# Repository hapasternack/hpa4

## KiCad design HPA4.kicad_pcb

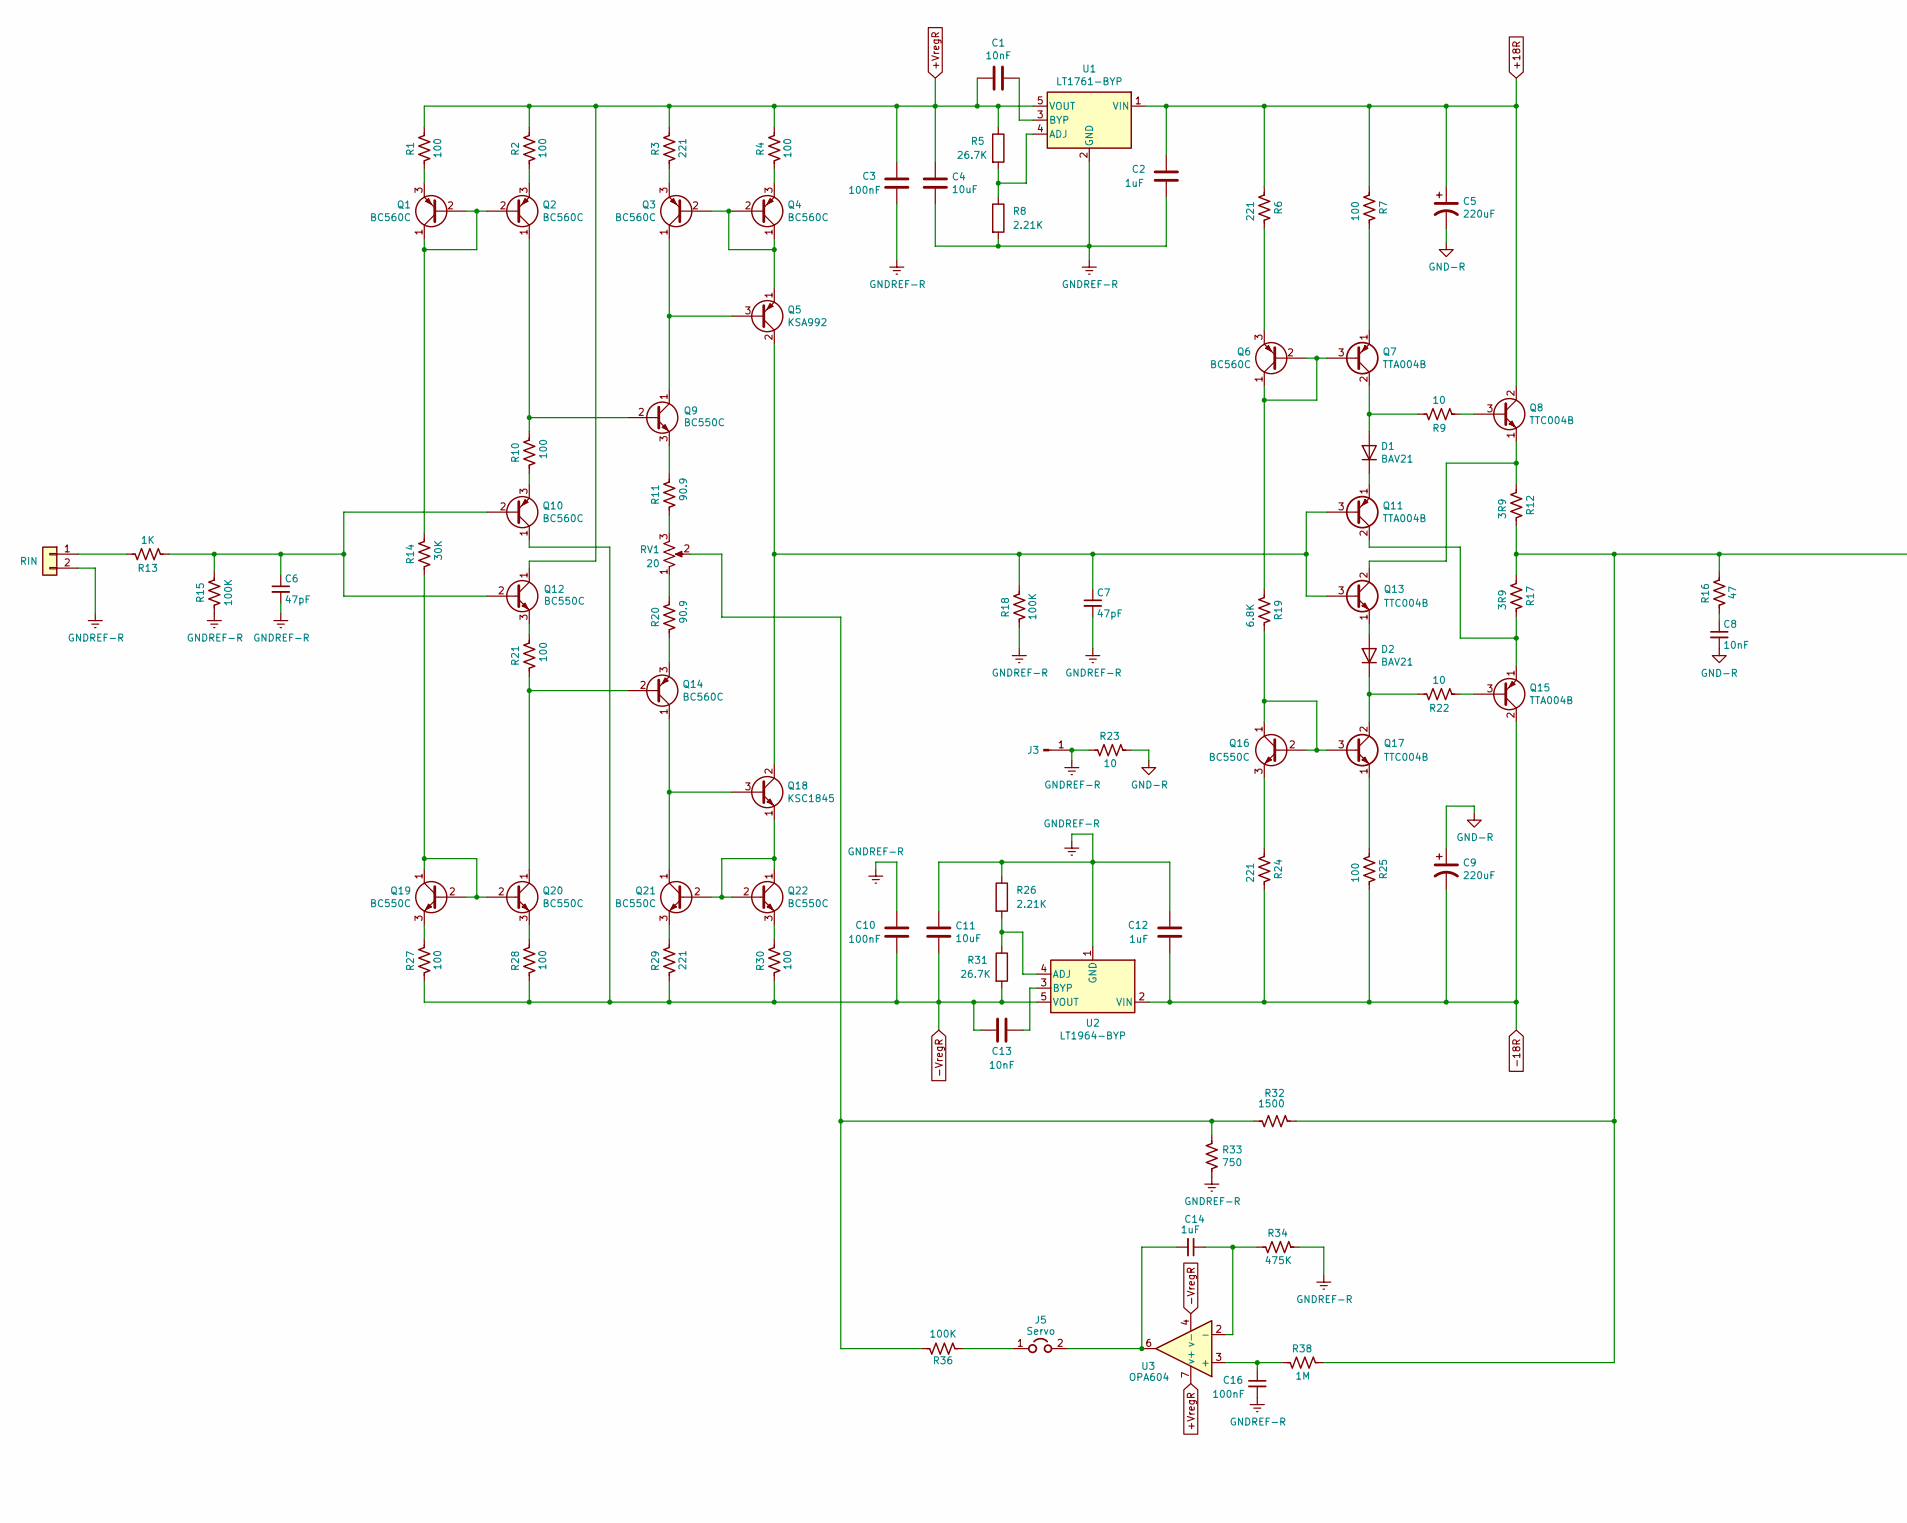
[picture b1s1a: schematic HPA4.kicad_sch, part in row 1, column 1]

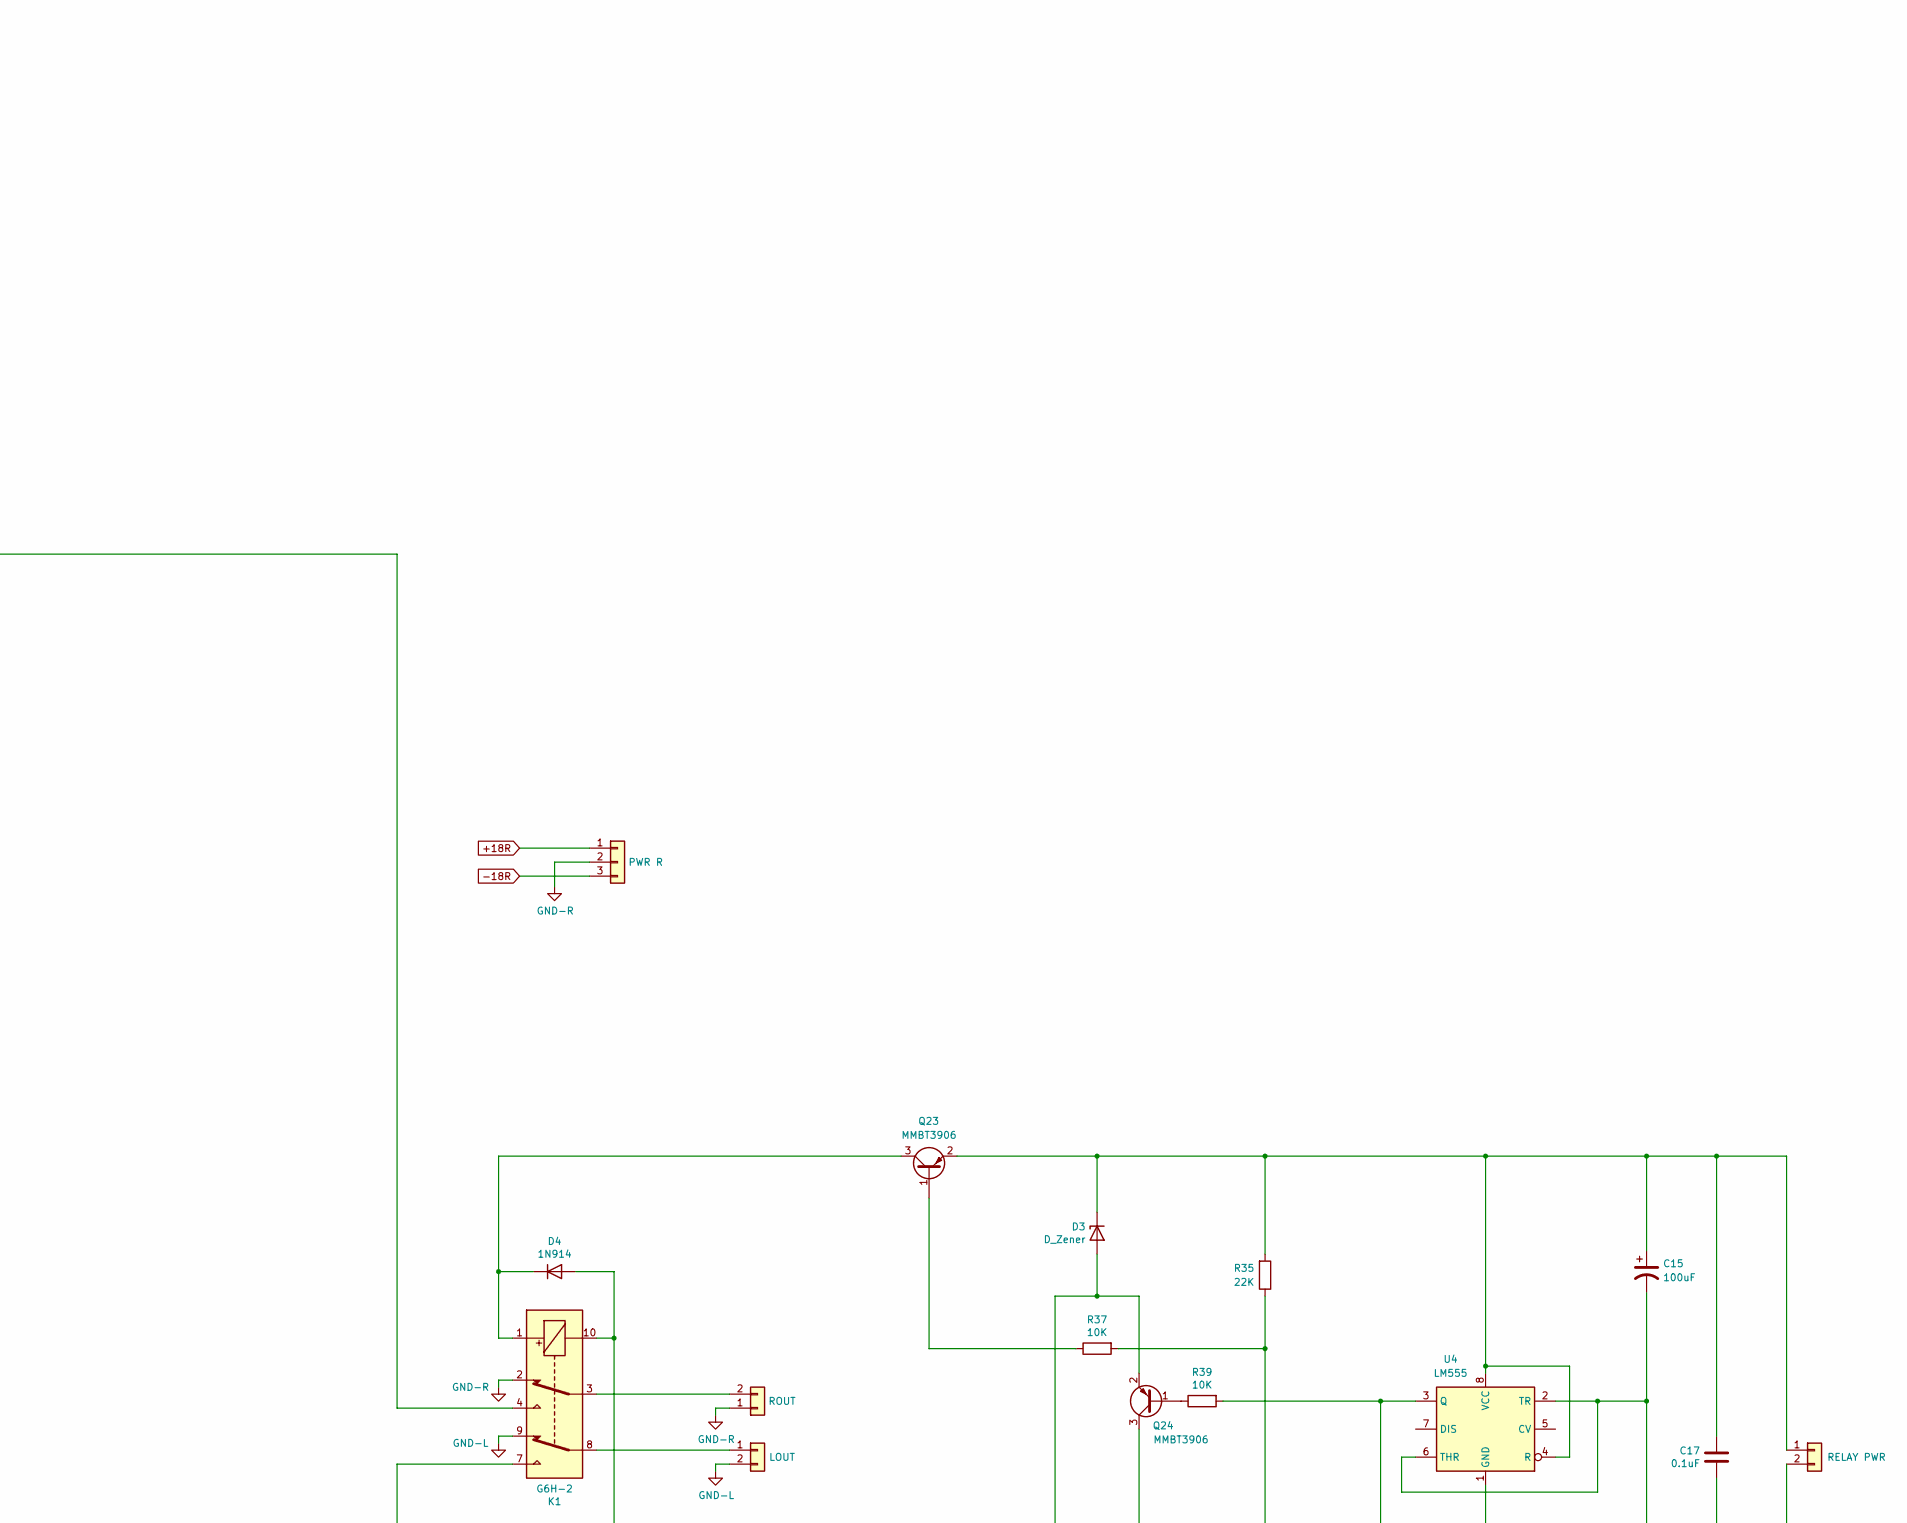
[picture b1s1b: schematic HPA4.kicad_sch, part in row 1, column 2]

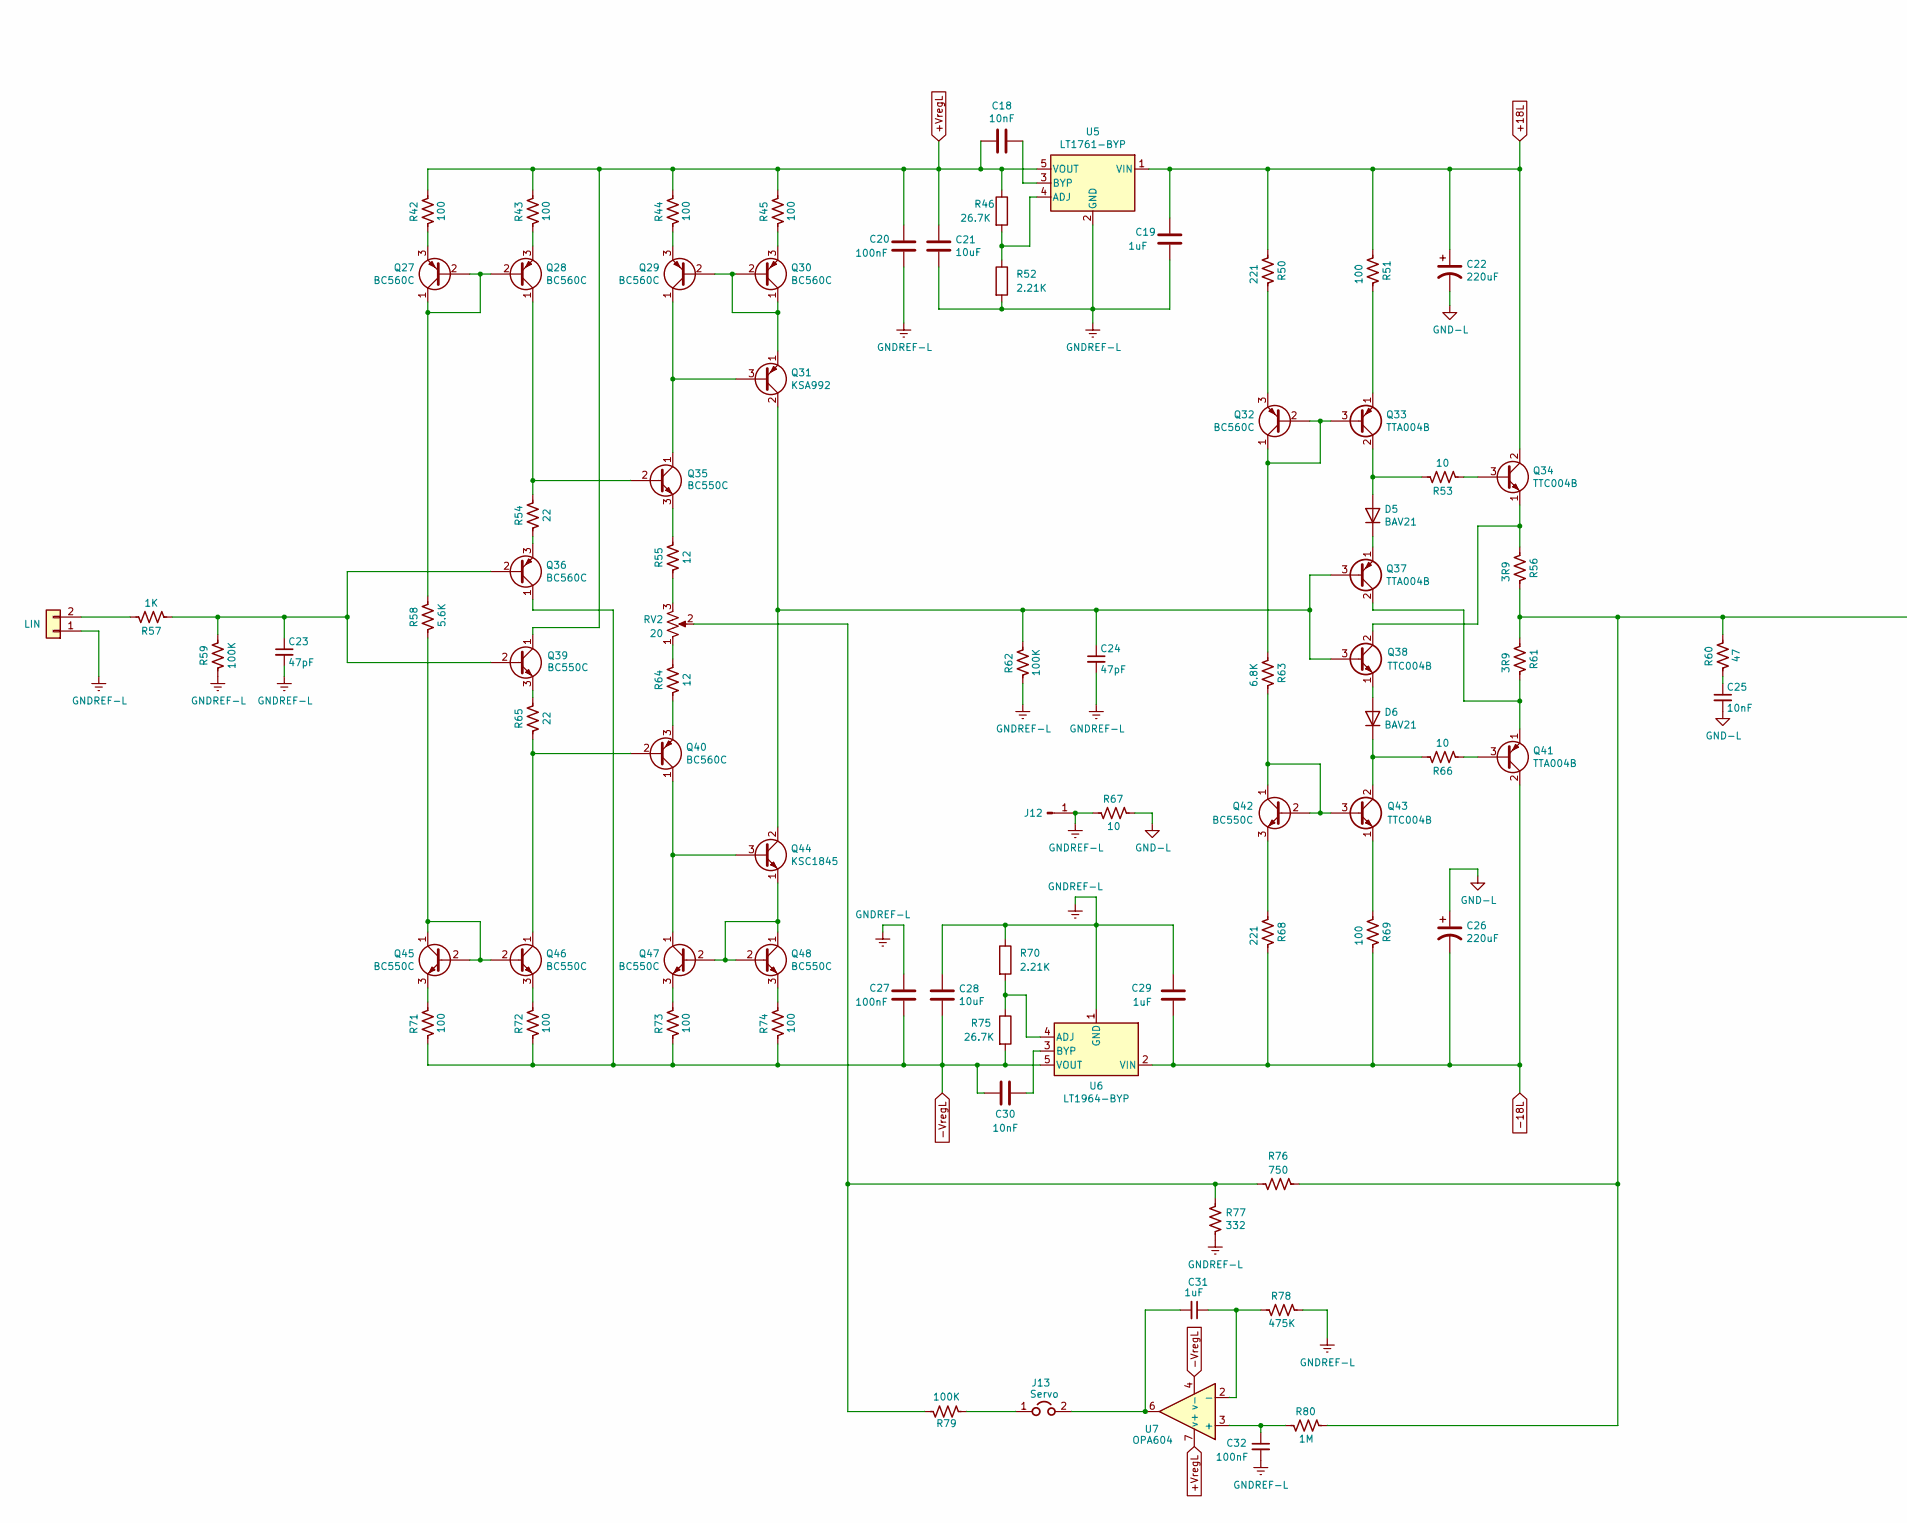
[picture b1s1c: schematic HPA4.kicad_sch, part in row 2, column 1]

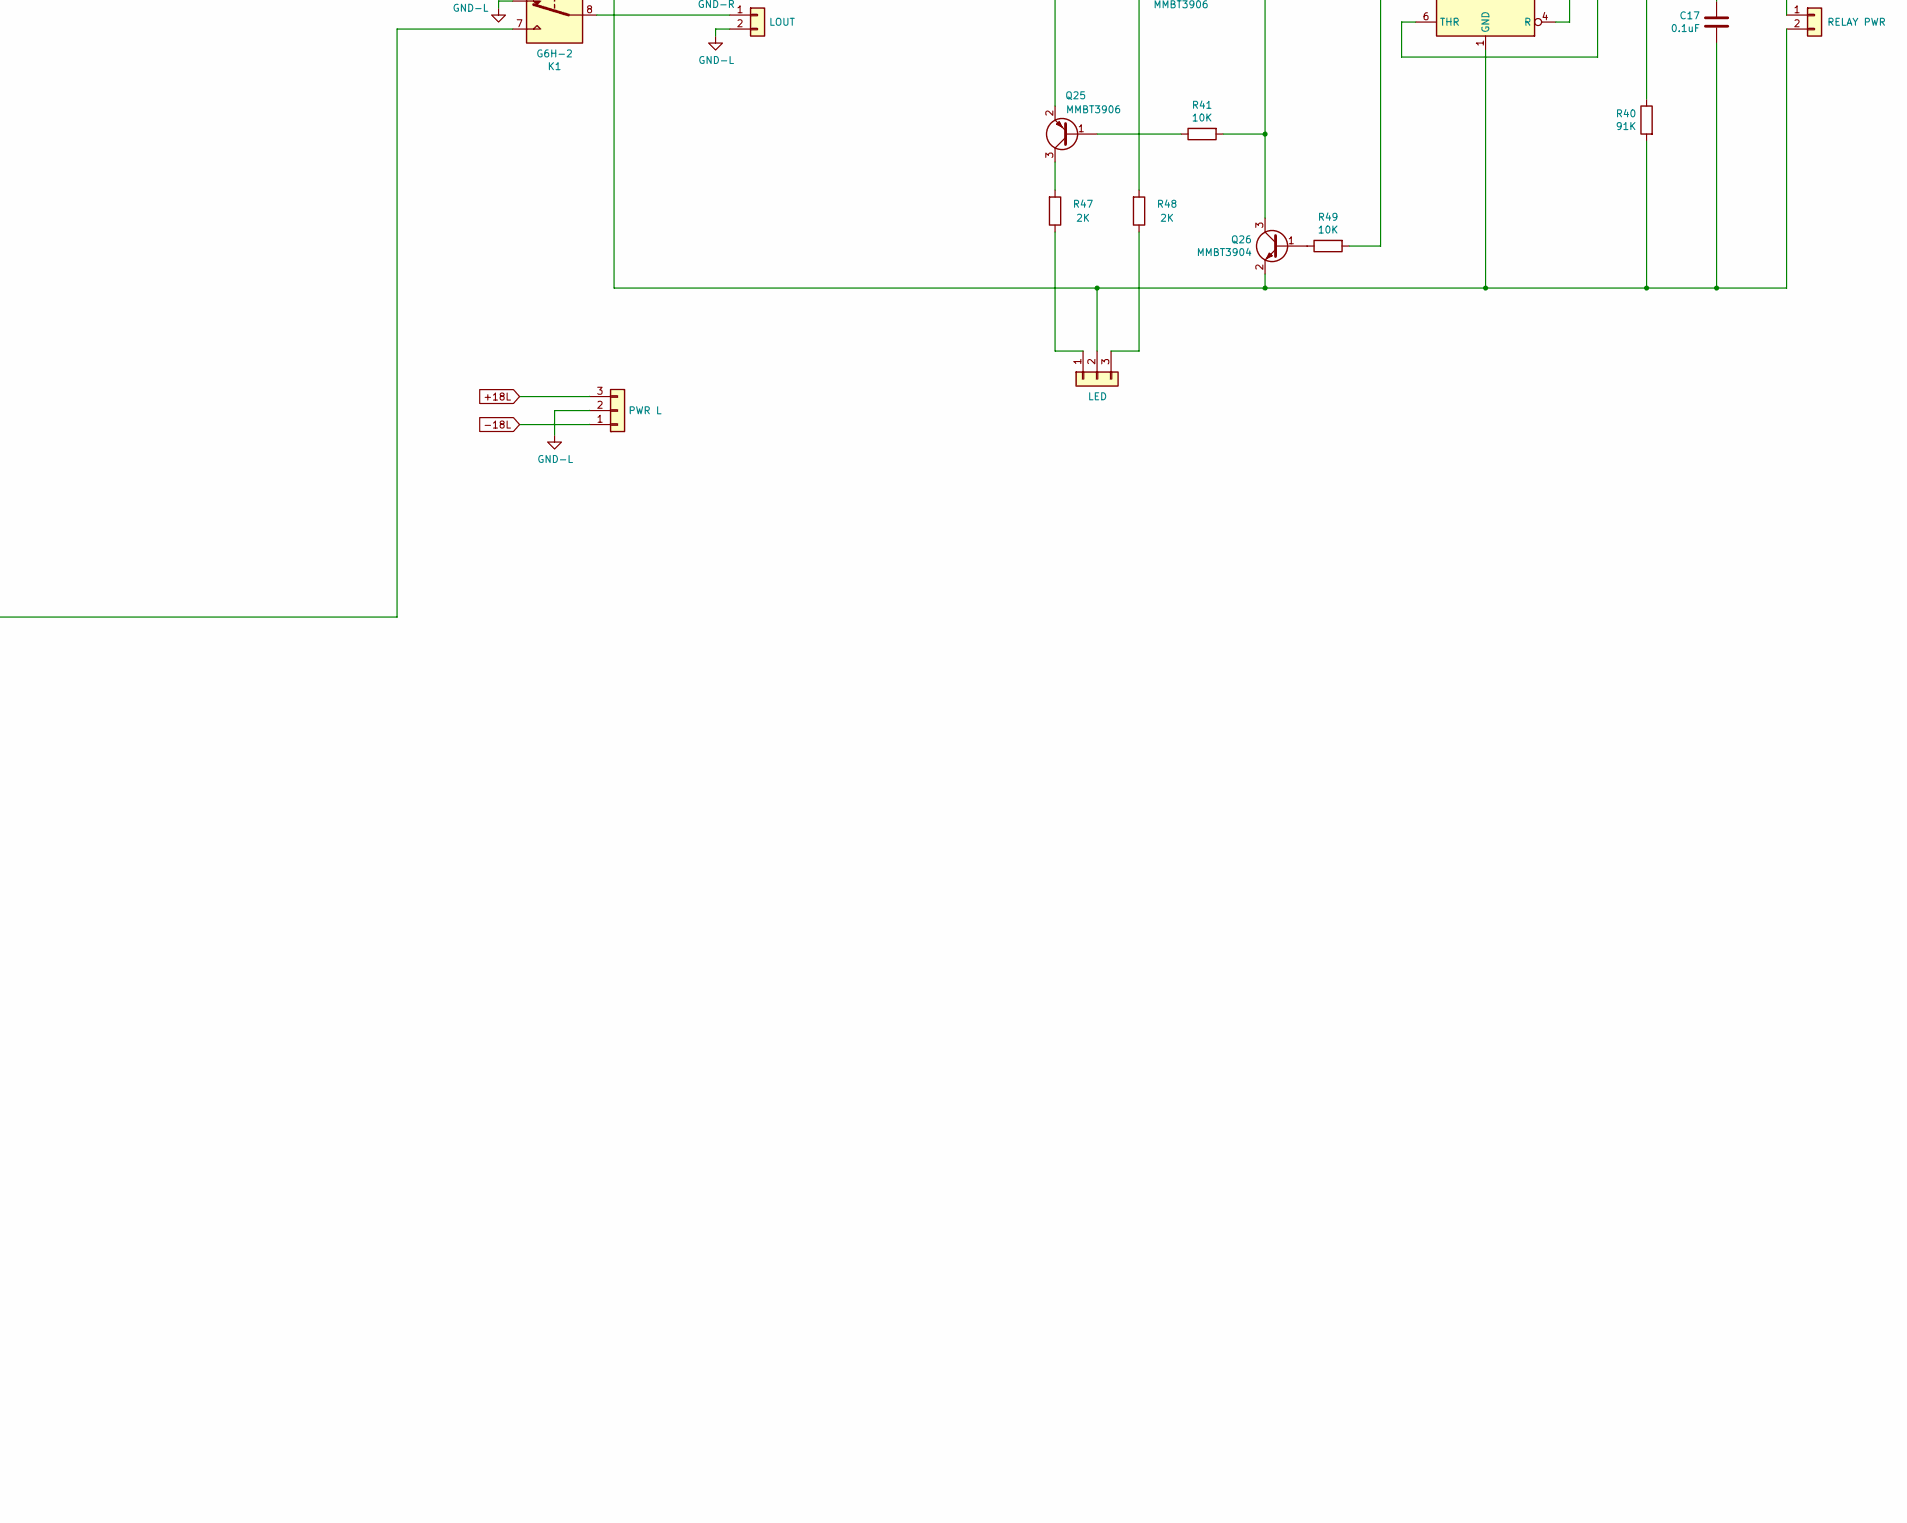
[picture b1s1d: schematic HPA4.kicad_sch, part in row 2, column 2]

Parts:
C1, C13, C18, C30: 10nF; C_0805_2012Metric
C2, C12, C19, C29: 1uF; C_0805_2012Metric
C3, C10, C16, C20, C27, C32: 100nF; C_Rect_L7.2mm_W2.5mm_P5.00mm_FKS2_FKP2_MKS2_MKP2
C4, C11, C21, C28: 10uF; C_0805_2012Metric
C5, C9, C22, C26: 220uF; CP_Radial_D10.0mm_P5.00mm
C6, C7, C23, C24: 47pF; C_Rect_L7.2mm_W4.5mm_P5.00mm_FKS2_FKP2_MKS2_MKP2
C8, C25: 10nF; C_Rect_L7.2mm_W2.5mm_P5.00mm_FKS2_FKP2_MKS2_MKP2
C14, C31: 1uF; C_Rect_L7.2mm_W5.5mm_P5.00mm_FKS2_FKP2_MKS2_MKP2
C15: 100uF; CP_Elec_5x5.9
C17: 0.1uF; C_1206_3216Metric_Pad1.33x1.80mm_HandSolder
D1, D2, D5, D6: BAV21; D_DO-35_SOD27_P7.62mm_Horizontal
D3: D_Zener; D_1206_3216Metric_Pad1.42x1.75mm_HandSolder
D4: 1N914; D_DO-35_SOD27_P7.62mm_Horizontal
J2: RIN; Molex-22-11-2022-2-Pin-Header
J3, J12: Conn_01x01_Male; 1-pad-wire-connector-22-ga
J4: PWR R; Molex-41791-0850-3-Pin-Header
J5, J13: Servo; PinHeader_1x02_P2.54mm_Vertical
J6: ROUT; Molex-41791-0849-2-Pin-Header
J7: LOUT; Molex-41791-0849-2-Pin-Header
J8: RELAY PWR; Molex-22-11-2022-2-Pin-Header
J9: LED; Molex-22-11-2032-3-Pin-Header
J10: PWR L; Molex-41791-0850-3-Pin-Header
J11: LIN; Molex-22-11-2022-2-Pin-Header
K1: G6H-2; Relay_DPDT_Omron_G6H-2
Q1, Q2, Q3, Q4, Q6, Q10, Q14, Q27, Q28, Q29, Q30, Q32, Q36, Q40: BC560C; TO-92
Q5, Q31: KSA992; TO-92
Q7, Q11, Q15, Q33, Q37, Q41: TTA004B; TO-126-3_Vertical
Q8, Q13, Q17, Q34, Q38, Q43: TTC004B; TO-126-3_Vertical
Q9, Q12, Q16, Q19, Q20, Q21, Q22, Q35, Q39, Q42, Q45, Q46, Q47, Q48: BC550C; TO-92
Q18, Q44: KSC1845; TO-92
Q23, Q24, Q25: MMBT3906; SOT-23
Q26: MMBT3904; SOT-23
R1, R2, R4, R7, R10, R21, R25, R27, R28, R30, R42, R43, R44, R45, R51, R69, R71, R72, R73, R74: 100; R_Axial_DIN0207_L6.3mm_D2.5mm_P10.16mm_Horizontal
R3, R6, R24, R29, R50, R68: 221; R_Axial_DIN0207_L6.3mm_D2.5mm_P10.16mm_Horizontal
R5, R31, R46, R75: 26.7K; R_0805_2012Metric
R8, R26, R52, R70: 2.21K; R_0805_2012Metric
R9, R22, R23, R53, R66, R67: 10; R_Axial_DIN0207_L6.3mm_D2.5mm_P10.16mm_Horizontal
R11, R20: 90.9; R_Axial_DIN0207_L6.3mm_D2.5mm_P10.16mm_Horizontal
R12, R17, R56, R61: 3R9; R_Axial_DIN0411_L9.9mm_D3.6mm_P12.70mm_Horizontal
R13, R57: 1K; R_Axial_DIN0207_L6.3mm_D2.5mm_P10.16mm_Horizontal
R14: 30K; R_Axial_DIN0207_L6.3mm_D2.5mm_P10.16mm_Horizontal
R15, R18, R36, R59, R62, R79: 100K; R_Axial_DIN0207_L6.3mm_D2.5mm_P10.16mm_Horizontal
R16, R60: 47; R_Axial_DIN0207_L6.3mm_D2.5mm_P10.16mm_Horizontal
R19, R63: 6.8K; R_Axial_DIN0207_L6.3mm_D2.5mm_P10.16mm_Horizontal
R32: 1500; R_Axial_DIN0207_L6.3mm_D2.5mm_P10.16mm_Horizontal
R33, R76: 750; R_Axial_DIN0207_L6.3mm_D2.5mm_P10.16mm_Horizontal
R34, R78: 475K; R_0805_2012Metric
R35: 22K; R_1206_3216Metric
R37, R39, R41, R49: 10K; R_1206_3216Metric
R38, R80: 1M; R_0805_2012Metric
R40: 91K; R_1206_3216Metric
R47, R48: 2K; R_1206_3216Metric
R54, R65: 22; R_Axial_DIN0207_L6.3mm_D2.5mm_P10.16mm_Horizontal
R55, R64: 12; R_Axial_DIN0207_L6.3mm_D2.5mm_P10.16mm_Horizontal
R58: 5.6K; R_Axial_DIN0207_L6.3mm_D2.5mm_P10.16mm_Horizontal
R77: 332; R_Axial_DIN0207_L6.3mm_D2.5mm_P10.16mm_Horizontal
RV1, RV2: 20; Potentiometer_Bourns_3296Y_Vertical
U1, U5: LT1761-BYP; TSOT-23-5
U2, U6: LT1964-BYP; TSOT-23-5
U3, U7: OPA604; SOIC-8_3.9x4.9mm_P1.27mm
U4: LM555; SOIC-8_3.9x4.9mm_P1.27mm

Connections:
+18L: C19.1, C22.1, J10.3, Q34.2 (C), R50.2, R51.2, U5.1 (VIN)
+18R: C2.1, C5.1, J4.1, Q8.2 (C), R6.2, R7.2, U1.1 (VIN)
+VregL: C18.2, C20.1, C21.1, Q39.1 (C), R42.1, R43.1, R44.1, R45.1, R46.1, U5.5 (VOUT), U7.7 (v+)
+VregR: C1.2, C3.1, C4.1, Q12.1 (C), R1.1, R2.1, R3.1, R4.1, R5.1, U1.5 (VOUT), U3.7 (v+)
-18L: C26.2, C29.1, J10.1, Q41.2 (C), R68.1, R69.1, U6.2 (VIN)
-18R: C9.2, C12.1, J4.3, Q15.2 (C), R24.1, R25.1, U2.2 (VIN)
-VregL: C27.2, C28.2, C30.2, Q36.1 (C), R71.2, R72.2, R73.2, R74.2, R75.2, U6.5 (VOUT), U7.4 (v-)
-VregR: C10.2, C11.2, C13.2, Q10.1 (C), R27.2, R28.2, R29.2, R30.2, R31.2, U2.5 (VOUT), U3.4 (v-)
GND-L: C22.2, C25.2, C26.1, J7.2, J10.2, K1.9, R67.1
GND-R: C5.2, C8.2, C9.1, J4.2, J6.1, K1.2, R23.1
GNDREF-L: C19.2, C20.2, C21.2, C23.2, C24.2, C27.1, C28.1, C29.2, C32.2, J11.1, J12.1, R52.2, R59.2, R62.2, R67.2, R70.1, R77.2, R78.1, U5.2 (GND), U6.1 (GND)
GNDREF-R: C2.2, C3.2, C4.2, C6.2, C7.2, C10.1, C11.1, C12.2, C16.2, J2.2, J3.1, R8.2, R15.2, R18.2, R23.2, R26.1, R33.2, R34.1, U1.2 (GND), U2.1 (GND)
unnamed: C1.1, U1.3 (BYP)
unnamed: C6.1, Q10.2 (B), Q12.2 (B), R13.2, R15.1
unnamed: C7.1, Q5.2 (C), Q11.3 (B), Q13.3 (B), Q18.2 (C), R18.1
unnamed: C8.1, R16.2
unnamed: C13.1, U2.3 (BYP)
unnamed: C14.1, R34.2, U3.2 (-)
unnamed: C14.2, J5.2, U3.6
unnamed: C15.1, C17.1, D3.1 (K), J8.1, Q23.2 (E), R35.2, U4.4 (R), U4.8 (VCC)
unnamed: C15.2, R40.1, U4.2 (TR), U4.6 (THR)
unnamed: C16.1, R38.2, U3.3 (+)
unnamed: C17.2, D4.2 (A), J8.2, J9.2, K1.10, Q26.2 (E), R40.2, U4.1 (GND)
unnamed: C18.1, U5.3 (BYP)
unnamed: C23.1, Q36.2 (B), Q39.2 (B), R57.2, R59.1
unnamed: C24.1, Q31.2 (C), Q37.3 (B), Q38.3 (B), Q44.2 (C), R62.1
unnamed: C25.1, R60.2
unnamed: C30.1, U6.3 (BYP)
unnamed: C31.1, R78.2, U7.2 (-)
unnamed: C31.2, J13.2, U7.6
unnamed: C32.1, R80.2, U7.3 (+)
unnamed: D1.1 (K), Q11.1 (E)
unnamed: D1.2 (A), Q7.2 (C), R9.1
unnamed: D2.1 (K), Q17.2 (C), R22.1
unnamed: D2.2 (A), Q13.1 (E)
unnamed: D3.2 (A), Q24.2 (E), Q25.2 (E)
unnamed: D4.1 (K), K1.1, Q23.3 (C)
unnamed: D5.1 (K), Q37.1 (E)
unnamed: D5.2 (A), Q33.2 (C), R53.1
unnamed: D6.1 (K), Q43.2 (C), R66.1
unnamed: D6.2 (A), Q38.1 (E)
unnamed: J2.1, R13.1
unnamed: J5.1, R36.1
unnamed: J6.2, K1.3
unnamed: J7.1, K1.8
unnamed: J9.1, R47.1
unnamed: J9.3, R48.1
unnamed: J11.2, R57.1
unnamed: J13.1, R79.1
unnamed: K1.4, R12.1, R16.1, R17.2, R32.2, R38.1
unnamed: K1.7, R56.1, R60.1, R61.2, R76.2, R80.1
unnamed: Q1.1 (C), Q1.2 (B), Q2.2 (B), R14.1
unnamed: Q1.3 (E), R1.2
unnamed: Q2.1 (C), Q9.2 (B), R10.1
unnamed: Q2.3 (E), R2.2
unnamed: Q3.1 (C), Q5.3 (B), Q9.1 (C)
unnamed: Q3.2 (B), Q4.1 (C), Q4.2 (B), Q5.1 (E)
unnamed: Q3.3 (E), R3.2
unnamed: Q4.3 (E), R4.2
unnamed: Q6.1 (C), Q6.2 (B), Q7.3 (B), R19.2
unnamed: Q6.3 (E), R6.1
unnamed: Q7.1 (E), R7.1
unnamed: Q8.3 (B), R9.2
unnamed: Q9.3 (E), R11.1
unnamed: Q10.3 (E), R10.2
unnamed: Q11.2 (C), Q15.1 (E), R17.1
unnamed: Q12.3 (E), R21.1
unnamed: Q8.1 (E), Q13.2 (C), R12.2
unnamed: Q14.1 (C), Q18.3 (B), Q21.1 (C)
unnamed: Q14.2 (B), Q20.1 (C), R21.2
unnamed: Q14.3 (E), R20.2
unnamed: Q15.3 (B), R22.2
unnamed: Q16.1 (C), Q16.2 (B), Q17.3 (B), R19.1
unnamed: Q16.3 (E), R24.2
unnamed: Q17.1 (E), R25.2
unnamed: Q18.1 (E), Q21.2 (B), Q22.1 (C), Q22.2 (B)
unnamed: Q19.1 (C), Q19.2 (B), Q20.2 (B), R14.2
unnamed: Q19.3 (E), R27.1
unnamed: Q20.3 (E), R28.1
unnamed: Q21.3 (E), R29.1
unnamed: Q22.3 (E), R30.1
unnamed: Q23.1 (B), R37.1
unnamed: Q24.1 (B), R39.1
unnamed: Q24.3 (C), R48.2
unnamed: Q25.1 (B), R41.1
unnamed: Q25.3 (C), R47.2
unnamed: Q26.1 (B), R49.1
unnamed: Q26.3 (C), R35.1, R37.2, R41.2
unnamed: Q27.1 (C), Q27.2 (B), Q28.2 (B), R58.1
unnamed: Q27.3 (E), R42.2
unnamed: Q28.1 (C), Q35.2 (B), R54.1
unnamed: Q28.3 (E), R43.2
unnamed: Q29.1 (C), Q31.3 (B), Q35.1 (C)
unnamed: Q29.2 (B), Q30.1 (C), Q30.2 (B), Q31.1 (E)
unnamed: Q29.3 (E), R44.2
unnamed: Q30.3 (E), R45.2
unnamed: Q32.1 (C), Q32.2 (B), Q33.3 (B), R63.2
unnamed: Q32.3 (E), R50.1
unnamed: Q33.1 (E), R51.1
unnamed: Q34.1 (E), Q38.2 (C), R56.2
unnamed: Q34.3 (B), R53.2
unnamed: Q35.3 (E), R55.1
unnamed: Q36.3 (E), R54.2
unnamed: Q37.2 (C), Q41.1 (E), R61.1
unnamed: Q39.3 (E), R65.1
unnamed: Q40.1 (C), Q44.3 (B), Q47.1 (C)
unnamed: Q40.2 (B), Q46.1 (C), R65.2
unnamed: Q40.3 (E), R64.2
unnamed: Q41.3 (B), R66.2
unnamed: Q42.1 (C), Q42.2 (B), Q43.3 (B), R63.1
unnamed: Q42.3 (E), R68.2
unnamed: Q43.1 (E), R69.2
unnamed: Q44.1 (E), Q47.2 (B), Q48.1 (C), Q48.2 (B)
unnamed: Q45.1 (C), Q45.2 (B), Q46.2 (B), R58.2
unnamed: Q45.3 (E), R71.1
unnamed: Q46.3 (E), R72.1
unnamed: Q47.3 (E), R73.1
unnamed: Q48.3 (E), R74.1
unnamed: R5.2, R8.1, U1.4 (ADJ)
unnamed: R11.2, RV1.3
unnamed: R20.1, RV1.1
unnamed: R26.2, R31.1, U2.4 (ADJ)
unnamed: R32.1, R33.1, R36.2, RV1.2
unnamed: R39.2, R49.2, U4.3 (Q)
unnamed: R46.2, R52.1, U5.4 (ADJ)
unnamed: R55.2, RV2.3
unnamed: R64.1, RV2.1
unnamed: R70.2, R75.1, U6.4 (ADJ)
unnamed: R76.1, R77.1, R79.2, RV2.2

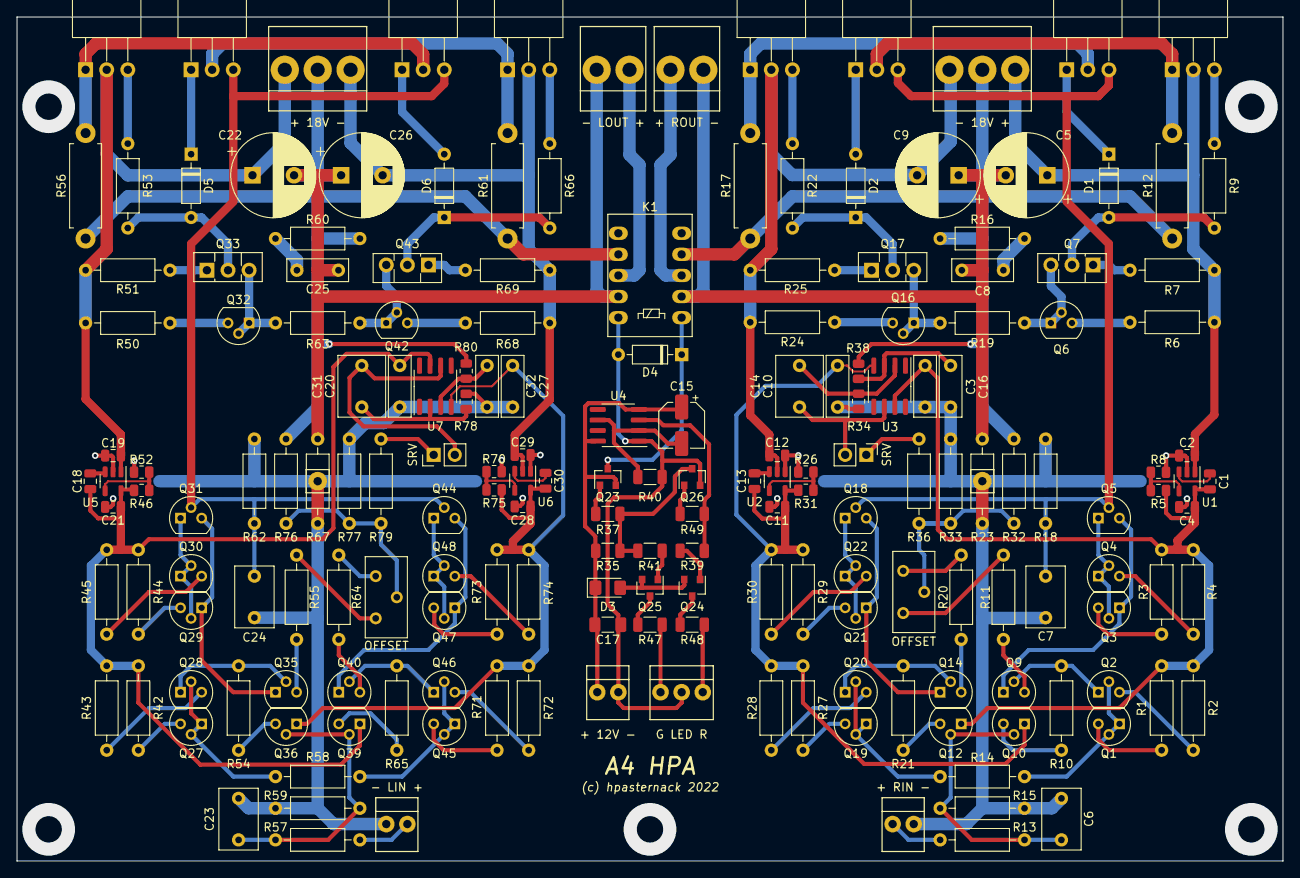
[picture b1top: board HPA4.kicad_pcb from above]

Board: 2 copper layers, 152.4 x 101.6 mm, 188 parts (0 on the bottom side), 129 nets.

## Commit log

2026-05-24 Corrected some incorrect resistor values in the left channel to match prior revisions to right channel.
